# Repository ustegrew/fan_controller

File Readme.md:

# Ventilator control for a laundry

A control system for a fan in a laundry drying room, to exchange humid air for dry air from outside.

## Repository structure

  * [Documentation::Wiki](https://github.com/ustegrew/fan_controller/wiki)
  * [Documentation::Files](https://github.com/ustegrew/fan_controller/tree/master/doc).

## Licenses

Source code is licensed under GPL3, all other content under FDL.

### Source code

    This program is free software: you can redistribute it and/or modify
    it under the terms of the GNU General Public License as published by
    the Free Software Foundation, either version 3 of the License, or
    (at your option) any later version.
	
    This program is distributed in the hope that it will be useful,
    but WITHOUT ANY WARRANTY; without even the implied warranty of
    MERCHANTABILITY or FITNESS FOR A PARTICULAR PURPOSE.  See the
    GNU General Public License for more details.
    
	You should have received a copy of the GNU General Public License
    along with this program.  If not, see <http://www.gnu.org/licenses/>.

### All other content

        Copyright (c)  2017  PETER HOPPE.
    Permission is granted to copy, distribute and/or modify this document
    under the terms of the GNU Free Documentation License, Version 1.3
    or any later version published by the Free Software Foundation;
    with no Invariant Sections, no Front-Cover Texts, and no Back-Cover Texts.
    A copy of the license is included in the section entitled "GNU
    Free Documentation License".

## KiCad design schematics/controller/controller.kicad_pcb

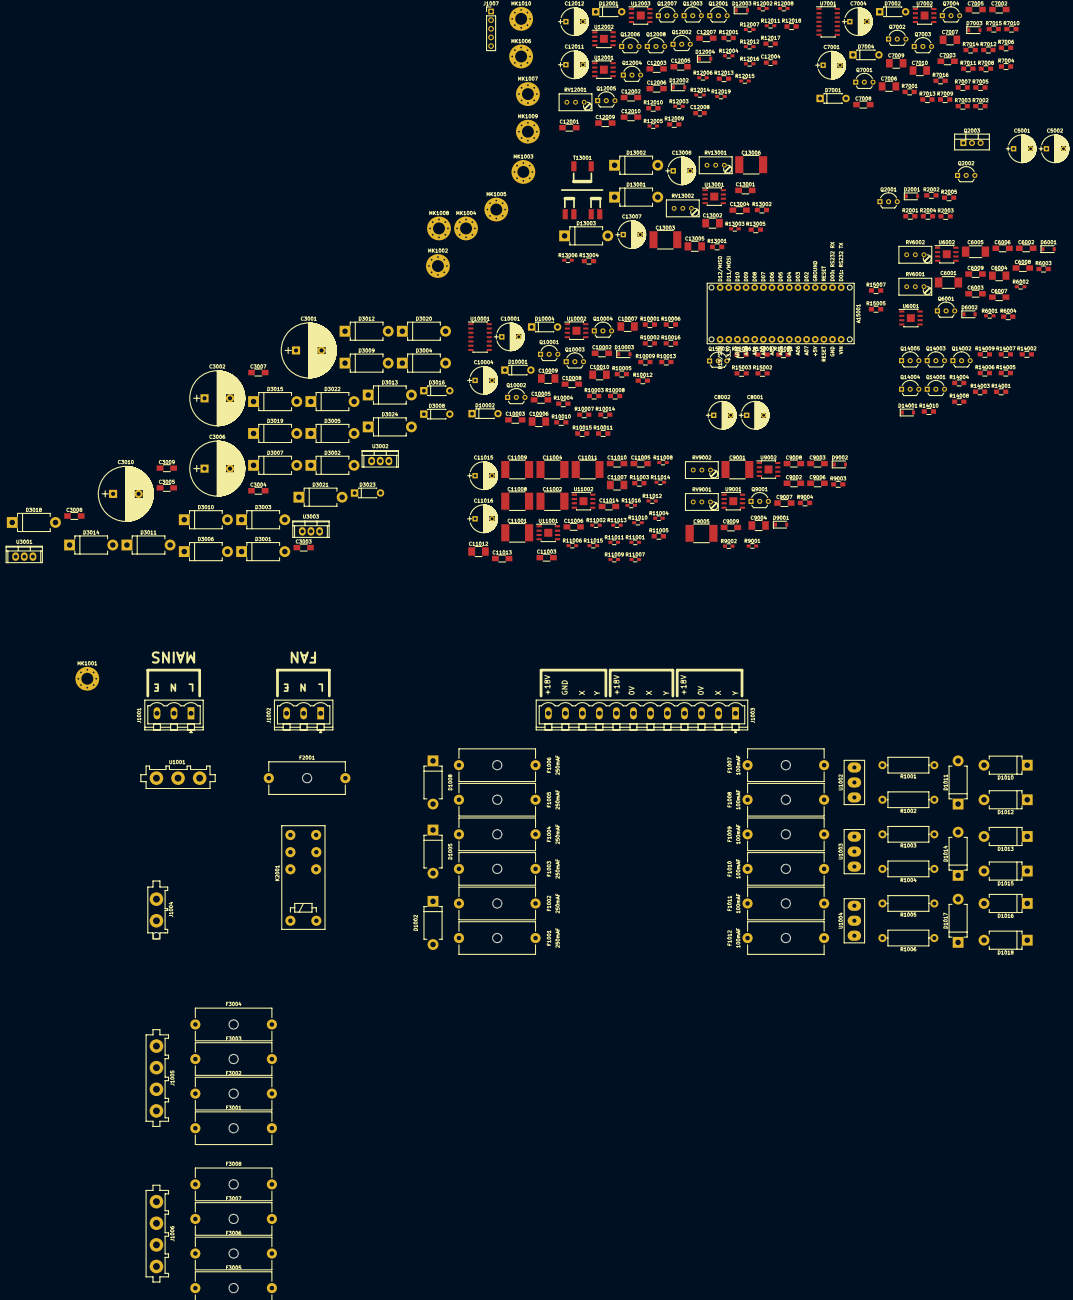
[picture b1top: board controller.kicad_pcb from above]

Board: 2 copper layers, 349 parts (0 on the bottom side), 195 nets, no tracks yet.

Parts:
A15001: Arduino_Nano_v3.x; arduino-nano_3.x
C3001: 1000uF/63V; CP_Radial_D16.0mm_P7.50mm
C3002, C3006, C3010: 470uF/63V; CP_Radial_D16.0mm_P7.50mm
C3003, C3007, C3008, C6002, C6003, C6006, C6007, C7002, C7003, C7005, C7008, C9002, C9003, C9006, C9007, C10002, C10003, C10005, C10008, C11005, C11006, C11013, C11014, C12001, C12002, C12003, C12005, C12006, C12007, C13001, C13004: 100nF; C_1206_HandSoldering
C3004, C3005, C3009, C6008, C9008, C12009, C12010: 1uF; C_1206_HandSoldering
C5001, C5002, C7001, C7004, C8001, C8002, C10001, C10004, C11015, C11016, C12011, C12012, C13007, C13008: 47uF / 63V; CP_Radial_D8.0mm_P5.00mm
C6001, C6005: 2.4nF; C_1812_HandSoldering
C6004, C7006, C7007, C7009, C7010, C9004, C10006, C10007, C10009, C10010, C11007, C11012, C13002, C13005: 4.7uF; C_1210_HandSoldering
C6009, C9009: 0.47uF; C_1206_HandSoldering
C9001, C9005, C11001, C11002, C11004, C11008, C11009, C11011: 1nF; C_2220_HandSoldering
C11003, C11010: 910pF; C_1206_HandSoldering
C12004: 0.22uF; C_0805_HandSoldering
C12008: 39nF; C_0805_HandSoldering
C13003, C13006: 4.7nF; C_2220_HandSoldering
D1002, D1005, D1008: 1.5KE33CA; D_DO-201AD_P12.70mm_Horizontal
D1010, D1011, D1012, D1013, D1014, D1015, D1016, D1017, D1018: 1.5KE30CA; D_DO-201AD_P12.70mm_Horizontal
D2001, D6001, D6002, D7003, D9001, D9002, D10003, D12002, D12003, D12004, D14001: 1N4148; D_SOD-123
D3001, D3004, D3007, D3009, D3012, D3015, D3020, D3024: 1.5KE36CA; D_DO-201AD_P12.70mm_Horizontal
D3002, D3003, D3005, D3006, D3010, D3011, D3013, D3014, D3018, D3019, D3021, D3022: 1N5404; D_DO-201AD_P12.70mm_Horizontal
D3008, D3016, D3023: 1N4007; D_DO-41_SOD81_P7.62mm_Horizontal
D7001, D7002, D7004, D10001, D10002, D10004: BZX85C5V6; D_DO-41_SOD81_P7.62mm_Horizontal
D12001: BZX85C6V2; D_DO-41_SOD81_P7.62mm_Horizontal
D13001, D13002, D13003: 1.5KE12CA; D_DO-201AD_P12.70mm_Horizontal
F1001, F1002, F1003, F1004, F1005, F1006: 250mAF; Fuseholder5x20_horiz_open_Schurter_0031_8201
F1007, F1008, F1009, F1010, F1011, F1012: 100mAF; Fuseholder5x20_horiz_open_Schurter_0031_8201
F2001: 6AT; Fuseholder5x20_horiz_open_Schurter_0031_8201
F3001, F3002: 2AT; Fuseholder5x20_horiz_open_Schurter_0031_8201
F3003, F3004: 1AT; Fuseholder5x20_horiz_open_Schurter_0031_8201
F3005, F3006, F3007, F3008: 1AF; Fuseholder5x20_horiz_open_Schurter_0031_8201
J1001, J1002: Screw_Terminal_01x03; PhoenixContact_MSTBVA-G_03x5.00mm_Vertical
J1003: Periphery; PhoenixContact_MSTBVA-G_12x5.00mm_Vertical
J1004: Conn_01x02_Male; TE_1969799-1
J1005, J1006: Conn_01x04_Male; TE_1969807-1
J1007: FRONTPANEL; Pin_Header_Straight_1x05_Pitch2.54mm
K2001: TE RT424024 (24VDC@1.44kOhm, DPDT, 250VAC, 8A); Relay_DPDT_Schrack-RT2-FormC_RM5.04mm
MK1001, MK1002, MK1003, MK1004, MK1005, MK1006, MK1007, MK1008, MK1009, MK1010: 3.5; MountingHole_3.5mm_Pad_Via
Q2001, Q7004, Q10004, Q12001, Q12002: BC556; TO-92_Inline_Wide
Q2002, Q7001, Q7002, Q7003, Q10001, Q10002, Q10003, Q12003, Q12004, Q12005, Q12006, Q12007, Q12008, Q14001, Q14002, Q14003, Q14004, Q14005, Q15001: BC546C; TO-92_Inline_Wide
Q2003: BD243C; TO-220-3_Vertical
Q6001, Q9001: 2N3819; TO-92_Inline_Wide
R1001, R1002, R1003, R1004, R1005, R1006: 27Ω / 1W; R_Axial_DIN0414_L11.9mm_D4.5mm_P15.24mm_Horizontal
R2001, R2005, R7005, R7006, R7008, R7009, R7016, R10005, R10006, R10008, R10009, R10016, R11003, R12009, R12010, R12013, R12017, R12018, R13004, R13005, R14002, R14003, R14007, R14009, R14010: 100kΩ; R_0805_HandSoldering
R2002, R2003, R7002, R7003, R7004, R7007, R10002, R10003, R10004, R10007, R13001, R13002, R14001, R14004, R14005, R14006, R14008, R15001, R15002, R15003, R15004, R15005, R15006, R15007: 10kΩ; R_0805_HandSoldering
R2004, R6003, R6004, R7001, R7010, R9003, R9004, R10001, R10010, R12001: 4.7kΩ; R_0805_HandSoldering
R6001, R6002: 4.42kΩ; R_0603_HandSoldering
R7011, R7012, R7013, R7014, R7015, R10011, R10012, R10013, R10014, R10015: 1kΩ; R_0805_HandSoldering
R9001, R9002: 6.34kΩ; R_0603_HandSoldering
R11001, R11004: 118kΩ; R_0603_HandSoldering
R11002: 133kΩ; R_0603_HandSoldering
R11005: 49.9kΩ; R_0805_HandSoldering
R11006: 56.2kΩ; R_0603_HandSoldering
R11007: 39.2kΩ; R_0603_HandSoldering
R11008: 46.4kΩ; R_0603_HandSoldering
R11009: 825Ω; R_0603_HandSoldering
R11010: 931Ω; R_0603_HandSoldering
R11011: 1.05kΩ; R_0603_HandSoldering
R11012: 23.7kΩ; R_0603_HandSoldering
R11013: 1.21kΩ; R_0603_HandSoldering
R11014: 27.4kΩ; R_0603_HandSoldering
R11015: 316Ω; R_0603_HandSoldering
R11016: 357Ω; R_0603_HandSoldering
R12002: 68kΩ; R_0603_HandSoldering
R12003, R12004, R12006, R12007, R12008: 22kΩ; R_0603_HandSoldering
R12005: 7.5kΩ; R_0603_HandSoldering
R12011, R12012, R12014, R12015, R12016, R12019: 39kΩ; R_0603_HandSoldering
R13003, R13006: 220Ω; R_0603_HandSoldering
RV6001, RV6002, RV9001, RV9002, RV12001, RV13001, RV13002: 22kΩ; Potentiometer_Trimmer_Bourns_3296W
T13001: Transformer_2P_1S; TRANSFORMER_VENDOR_VACUUMSCHMELZE_T60403-K5032-X102
U1001: Module: surgeprot.mains.275.5.01; TE_1969803-1
U1002, U1003, U1004: Bourns 2026-07-C2LF; Bourns_2026-xx
U3001: L7805; TO-220
U3002: L7815; TO-220
U3003: L7915; TO-220
U6001, U6002, U7002, U9001, U9002, U10002, U12001, U12002, U12003: TL061; SOIC-8-1EP_3.9x4.9mm_Pitch1.27mm
U7001, U10001: 4066; SOIC-14_3.9x8.7mm_Pitch1.27mm
U11001, U11002, U13001: OP282; SOIC-8-1EP_3.9x4.9mm_Pitch1.27mm

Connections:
/comms/DETECTOR_15K_10BAUD_SDA: D14001.2, Q12004.1, Q14003.1, R14005.2
/comms/OSC_15K_UNMUTE_10BAUD_SDA: D7002.1, Q14004.1, R14006.1
/comms/OSC_25K_UNMUTE_10BAUD_SCL: D10002.1, Q14001.3, R14003.1
/comms/VCC: C3005.1, C5001.1, C6002.1, C6003.1, C7005.2, C8001.1, C9002.1, C9003.1, C10005.2, C11005.1, C11006.1, C11015.1, C12001.2, C12003.2, C12005.2, C12011.1, C13001.1, C13007.1, D3016.2, D12001.2, Q7001.1, Q10001.1, R7001.1, R10001.1, R12001.1, R12002.1, R12011.1, R12012.1, R12014.1, R12015.1, U3002.3, U6001.7, U6002.7, U7002.7, U9001.7, U9002.7, U10002.7, U11001.8, U11002.8, U12001.7, U12002.7, U12003.7, U13001.8
/comms/VEE: C3009.2, C5002.2, C6006.1, C6007.1, C7008.2, C8002.2, C9006.1, C9007.1, C10008.2, C11013.1, C11014.1, C11016.2, C12002.2, C12006.2, C12007.2, C12012.2, C13004.1, C13008.2, D3023.1, Q7004.1, Q10004.1, R7010.2, R10010.2, U3003.3, U6001.4, U6002.4, U7002.4, U9001.4, U9002.4, U10002.4, U11001.4, U11002.4, U12001.4, U12002.4, U12003.4, U13001.4
/comms/X: D1010.2, D1011.2, D1013.2, D1014.2, D1016.2, D1017.2, R1001.1, R1003.1, R1005.1, T13001.1
/comms/Y: D1011.1, D1012.2, D1014.1, D1015.2, D1017.1, D1018.2, R1002.1, R1004.1, R1006.1, T13001.2
/comms/comms/barrier/OSC_15K_SIG_OUT_10BAUD_SDA: C7007.1, R13001.2
/comms/comms/barrier/OSC_25K_SIG_OUT_10BAUD_SCL: C10007.1, R13002.2
/comms/comms/detector_15k/IN: C11012.2, C12004.2
/comms/comms/filter_15k/IN: C11007.1, RV13002.3, U13001.7
/comms/comms/osc_15k/osc_15k/osc/OUT: C6004.1, R7011.2
/comms/comms/osc_25k/osc_25k/osc/OUT: C9004.1, R10011.2
/comms_router/CPU_10BAUD_SCL: A15001.6, R14001.2, R15005.2
/comms_router/CPU_10BAUD_SDA: A15001.5, R14004.2, R15006.2
/comms_router/CPU_10BAUD_WR_EN: A15001.7, R14008.2, R15004.2
/comms_router/V_LOGIC: A15001.27, C3004.1, D3008.2, J1007.4, Q14001.1, Q14002.1, R14005.1, R14007.1, R15001.1, R15002.1, R15003.1, R15004.1, R15005.1, R15006.1, U3001.3
/cpu/CPU_HIBAUD_SCL: A15001.24, J1007.1, R15001.2
/cpu/CPU_HIBAUD_SDA: A15001.23, J1007.2, R15002.2
/cpu/FAN_ON: A15001.8, R2003.1, R15003.2
/cpu/RESET: J1007.3, R15007.1
/fan-switch/L: F2001.1, J1001.1, U1001.1
/fan-switch/LFAN: J1002.1, K2001.24
/fan-switch/N: J1001.2, J1004.1, K2001.11, U1001.2
/fan-switch/NFAN: J1002.2, K2001.14
/psu/TR01-1: F3001.1, J1005.1
/psu/TR01-2: F3002.1, J1005.2
/psu/TR01-3: F3003.1, J1005.3
/psu/TR01-4: F3004.1, J1005.4
/psu/TR02-1: F3005.1, J1006.1
/psu/TR02-2: F3006.1, J1006.2
/psu/TR02-3: F3007.1, J1006.3
/psu/TR02-4: F3008.1, J1006.4
/psu/V_DCDC_+18: C3001.1, D1002.2, D1005.2, D1008.2, D2001.1, D3003.1, D3006.1, F1001.1, F1003.1, F1005.1, K2001.A2, Q2001.3, R2001.1
Earth: A15001.4, A15001.29, C3001.2, C3002.2, C3003.2, C3004.2, C3005.2, C3006.2, C3007.2, C3008.1, C3009.1, C3010.1, C5001.2, C5002.1, C6002.2, C6003.2, C6006.2, C6007.2, C7001.2, C7002.2, C7003.1, C7004.1, C7005.1, C7008.1, C7009.2, C7010.2, C8001.2, C8002.1, C9002.2, C9003.2, C9006.2, C9007.2, C10001.2, C10002.2, C10003.1, C10004.1, C10005.1, C10008.1, C10009.2, C10010.2, C11005.2, C11006.2, C11013.2, C11014.2, C11015.2, C11016.1, C12001.1, C12002.1, C12003.1, C12005.1, C12006.1, C12007.1, C12008.2, C12009.2, C12010.2, C12011.2, C12012.1, C13001.2, C13003.1, C13004.2, C13006.1, C13007.2, C13008.1, D1002.1, D1005.1, D1008.1, D1010.1, D1012.1, D1013.1, D1015.1, D1016.1, D1018.1, D3001.1, D3002.2, D3005.2, D3007.2, D3009.1, D3010.2, D3013.2, D3015.2, D3020.1, D3024.2, D7001.2, D7004.1, D10001.2, D10004.1, D13001.2, D13003.1, F1002.1, F1004.1, F1006.1, F3006.2, F3007.2, J1001.3, J1002.3, J1007.5, MK1001.1, MK1002.1, MK1003.1, MK1004.1, MK1005.1, MK1006.1, MK1007.1, MK1008.1, MK1009.1, MK1010.1, Q2002.3, Q2003.3, Q12002.1, Q12003.3, Q12004.3, Q12007.3, Q12008.3, Q14003.3, Q14004.3, Q14005.3, Q15001.3, R2005.2, R7016.2, R10016.2, R11009.2, R11010.2, R11011.2, R11013.2, R11015.2, R11016.2, R12004.2, R12008.2, R12009.2, R12010.2, R12016.2, R12019.2, R13004.1, R13005.2, R14002.2, R14003.2, R14009.2, R14010.2, RV12001.3, RV13001.3, RV13002.1, T13001.4, T13001.5, U1002.2, U1003.2, U1004.2, U3001.2, U3002.2, U3003.1, U11001.3, U11001.5
unnamed: A15001.3, A15001.28, Q15001.1
unnamed: C3002.1, C3003.1, D3008.1, D3011.1, D3014.1, U3001.1
unnamed: C3006.1, C3007.1, D3016.1, D3019.1, D3022.1, U3002.1
unnamed: C3008.2, C3010.2, D3018.2, D3021.2, D3023.2, U3003.2
unnamed: C6001.1, R6003.1, RV6001.1, U6001.6, U6002.3
unnamed: C6001.2, R6001.1
unnamed: C6004.2, U6002.2, U6002.6
unnamed: C6005.1, R6001.2, R6002.1, U6001.3
unnamed: C6005.2, C6009.2, D6002.1, Q6001.3, R6002.2, R6004.2, RV6002.3
unnamed: C6008.1, R6003.2
unnamed: C6008.2, D6001.1, D6002.2
unnamed: C6009.1, D6001.2, R6004.1, RV6002.1
unnamed: C7001.1, D7001.1, R7001.2, R7002.2
unnamed: C7002.1, Q7001.3, R7003.1, R7004.1, U7001.14
unnamed: C7003.2, D7003.2, Q7002.3, Q7003.3, Q7004.3, U7001.7
unnamed: C7004.2, D7004.2, R7007.2, R7010.1
unnamed: C7006.1, R7016.1, U7002.3
unnamed: C7006.2, R7015.1
unnamed: C7007.2, U7002.2, U7002.6
unnamed: C7009.1, U7001.9
unnamed: C7010.1, U7001.10
unnamed: C9001.1, R9003.1, RV9001.1, U9001.6, U9002.3
unnamed: C9001.2, R9001.1
unnamed: C9004.2, U9002.2, U9002.6
unnamed: C9005.1, R9001.2, R9002.1, U9001.3
unnamed: C9005.2, C9009.2, D9002.1, Q9001.3, R9002.2, R9004.2, RV9002.3
unnamed: C9008.1, R9003.2
unnamed: C9008.2, D9001.1, D9002.2
unnamed: C9009.1, D9001.2, R9004.1, RV9002.1
unnamed: C10001.1, D10001.1, R10001.2, R10002.2
unnamed: C10002.1, Q10001.3, R10003.1, R10004.1, U10001.14
unnamed: C10003.2, D10003.2, Q10002.3, Q10003.3, Q10004.3, U10001.7
unnamed: C10004.2, D10004.2, R10007.2, R10010.1
unnamed: C10006.1, R10016.1, U10002.3
unnamed: C10006.2, R10015.1
unnamed: C10007.2, U10002.2, U10002.6
unnamed: C10009.1, U10001.9
unnamed: C10010.1, U10001.10
unnamed: C11001.1, C11008.1, R11005.2, R11009.1
unnamed: C11001.2, R11001.1, R11006.1, U11001.1
unnamed: C11002.1, C11009.1, R11006.2, R11010.1
unnamed: C11002.2, R11002.1, R11007.1, U11001.7
unnamed: C11003.1, C11010.1, R11007.2, R11011.1
unnamed: C11003.2, R11003.1, R11008.1, R11012.1, U11002.1
unnamed: C11004.1, C11011.1, R11008.2, R11013.1
unnamed: C11004.2, C11012.1, R11004.1, R11014.1, U11002.7
unnamed: C11007.2, R11005.1
unnamed: C11008.2, R11001.2, U11001.2
unnamed: C11009.2, R11002.2, U11001.6
unnamed: C11010.2, R11003.2, U11002.2
unnamed: C11011.2, R11004.2, U11002.6
unnamed: C12004.1, R12009.1, U12002.3
unnamed: C12008.1, Q12001.1, Q12003.1, U12001.3, U12003.2
unnamed: C12009.1, Q12005.2, R12014.2, R12016.1
unnamed: C12010.1, Q12006.2, R12015.2, R12019.1
unnamed: C13002.1, C13003.2, R13003.2
unnamed: C13002.2, RV13001.1, U13001.1
unnamed: C13005.1, C13006.2, R13006.1
unnamed: C13005.2, R13005.1, U13001.5
unnamed: D2001.2, K2001.A1, Q2003.2
unnamed: D3001.2, D3002.1, D3003.2, D3004.2, F3001.2
unnamed: D3004.1, D3005.1, D3006.2, D3007.1, F3002.2
unnamed: D3009.2, D3010.1, D3011.2, D3012.2, F3003.2
unnamed: D3012.1, D3013.1, D3014.2, D3015.1, F3004.2
unnamed: D3018.1, D3019.2, D3020.2, F3005.2
unnamed: D3021.1, D3022.2, D3024.1, F3008.2
unnamed: D7002.2, R7005.2
unnamed: D7003.1, Q7002.2, R7005.1
unnamed: D10002.2, R10005.2
unnamed: D10003.1, Q10002.2, R10005.1
unnamed: D12001.1, Q12002.2, R12004.1
unnamed: D12002.1, Q12008.2, R12018.2
unnamed: D12002.2, R12003.2
unnamed: D12003.1, Q12007.2, R12017.1
unnamed: D12003.2, R12007.2
unnamed: D12004.1, Q12003.2, R12010.1
unnamed: D12004.2, R12006.2
unnamed: D13001.1, D13002.1, R13003.1, T13001.3
unnamed: D13002.2, D13003.2, R13006.2, T13001.6
unnamed: D14001.1, Q14002.2, R14004.1
unnamed: F1001.2, J1003.1
unnamed: F1002.2, J1003.2
unnamed: F1003.2, J1003.5
unnamed: F1004.2, J1003.6
unnamed: F1005.2, J1003.9
unnamed: F1006.2, J1003.10
unnamed: F1007.1, R1001.2, U1002.1
unnamed: F1007.2, J1003.3
unnamed: F1008.1, R1002.2, U1002.3
unnamed: F1008.2, J1003.4
unnamed: F1009.1, R1003.2, U1003.1
unnamed: F1009.2, J1003.7
unnamed: F1010.1, R1004.2, U1003.3
unnamed: F1010.2, J1003.8
unnamed: F1011.1, R1005.2, U1004.1
unnamed: F1011.2, J1003.11
unnamed: F1012.1, R1006.2, U1004.3
unnamed: F1012.2, J1003.12
unnamed: F2001.2, K2001.21
unnamed: J1004.2, U1001.3
unnamed: Q2001.1, R2004.1, R2005.1
unnamed: Q2001.2, R2002.2
unnamed: Q2002.1, R2001.2, R2002.1
unnamed: Q2002.2, R2003.2
unnamed: Q2003.1, R2004.2
unnamed: Q6001.1, RV6001.3
unnamed: Q6001.2, RV6002.2
unnamed: Q7001.2, R7002.1
unnamed: Q7002.1, R7003.2, R7006.2, R7008.1
unnamed: Q7003.1, R7004.2, R7009.1
unnamed: Q7003.2, R7006.1
unnamed: Q7004.2, R7007.1
unnamed: Q9001.1, RV9001.3
unnamed: Q9001.2, RV9002.2
unnamed: Q10001.2, R10002.1
unnamed: Q10002.1, R10003.2, R10006.2, R10008.1
unnamed: Q10003.1, R10004.2, R10009.1
unnamed: Q10003.2, R10006.1
unnamed: Q10004.2, R10007.1
unnamed: Q12001.2, Q12002.3
unnamed: Q12001.3, R12001.2
unnamed: Q12004.2, R12013.2
unnamed: Q12005.1, R12011.2, R12018.1
unnamed: Q12005.3, Q12007.1
unnamed: Q12006.1, R12012.2, R12013.1, R12017.2
unnamed: Q12006.3, Q12008.1
unnamed: Q14001.2, R14001.1, R14002.1
unnamed: Q14002.3, R14006.2, R14010.1
unnamed: Q14003.2, Q14005.2, R14008.1, R14009.1
unnamed: Q14004.2, Q14005.1, R14007.2
unnamed: Q15001.2, R15007.2
unnamed: R7008.2, U7001.5, U7001.13
unnamed: R7009.2, U7001.6, U7001.12
unnamed: R7011.1, U7001.1
unnamed: R7012.1, R7013.2, U7001.8
unnamed: R7012.2, U7001.2
unnamed: R7013.1, U7001.4
unnamed: R7014.1, R7015.2, U7001.11
unnamed: R7014.2, U7001.3
unnamed: R10008.2, U10001.5, U10001.13
unnamed: R10009.2, U10001.6, U10001.12
unnamed: R10011.1, U10001.1
unnamed: R10012.1, R10013.2, U10001.8
unnamed: R10012.2, U10001.2
unnamed: R10013.1, U10001.4
unnamed: R10014.1, R10015.2, U10001.11
unnamed: R10014.2, U10001.3
unnamed: R11012.2, R11015.1, U11002.3
unnamed: R11014.2, R11016.1, U11002.5
unnamed: R12002.2, R12005.1, U12001.2
unnamed: R12003.1, U12001.6
unnamed: R12005.2, R12008.1, U12003.3
unnamed: R12006.1, RV12001.1, U12002.6
unnamed: R12007.1, U12003.6
unnamed: R13001.1, R13002.1, R13004.2, U13001.3
unnamed: RV6001.2, U6001.2
unnamed: RV9001.2, U9001.2
unnamed: RV12001.2, U12002.2
unnamed: RV13001.2, U13001.2
unnamed: RV13002.2, U13001.6

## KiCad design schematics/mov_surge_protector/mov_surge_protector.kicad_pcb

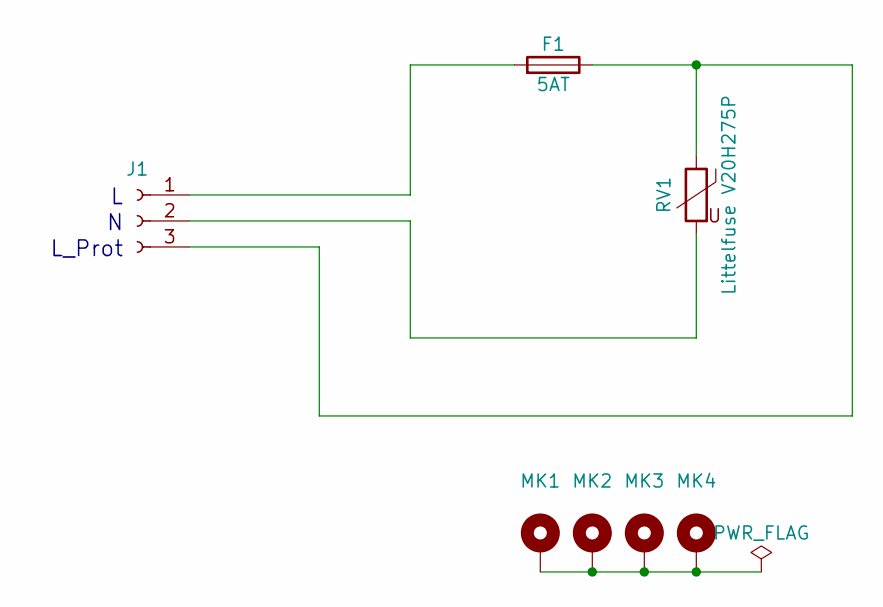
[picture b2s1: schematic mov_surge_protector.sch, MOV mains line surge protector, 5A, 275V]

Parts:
F1: 5AT; Fuseholder5x20_horiz_open_lateral_Type-II
J1: Conn_01x03_Female; MOV_Surge_Protector
MK1, MK2, MK3, MK4: Mounting_Hole_PAD; SolderWirePad_single_1-5mmDrill
RV1: Littelfuse V20H275P; RV_Disc_D21.5_W5.6_P10

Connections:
unnamed: F1.1, J1.3, RV1.1
unnamed: F1.2, J1.1
unnamed: J1.2, RV1.2
unnamed: MK1.1, MK2.1, MK3.1, MK4.1

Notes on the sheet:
L_Prot

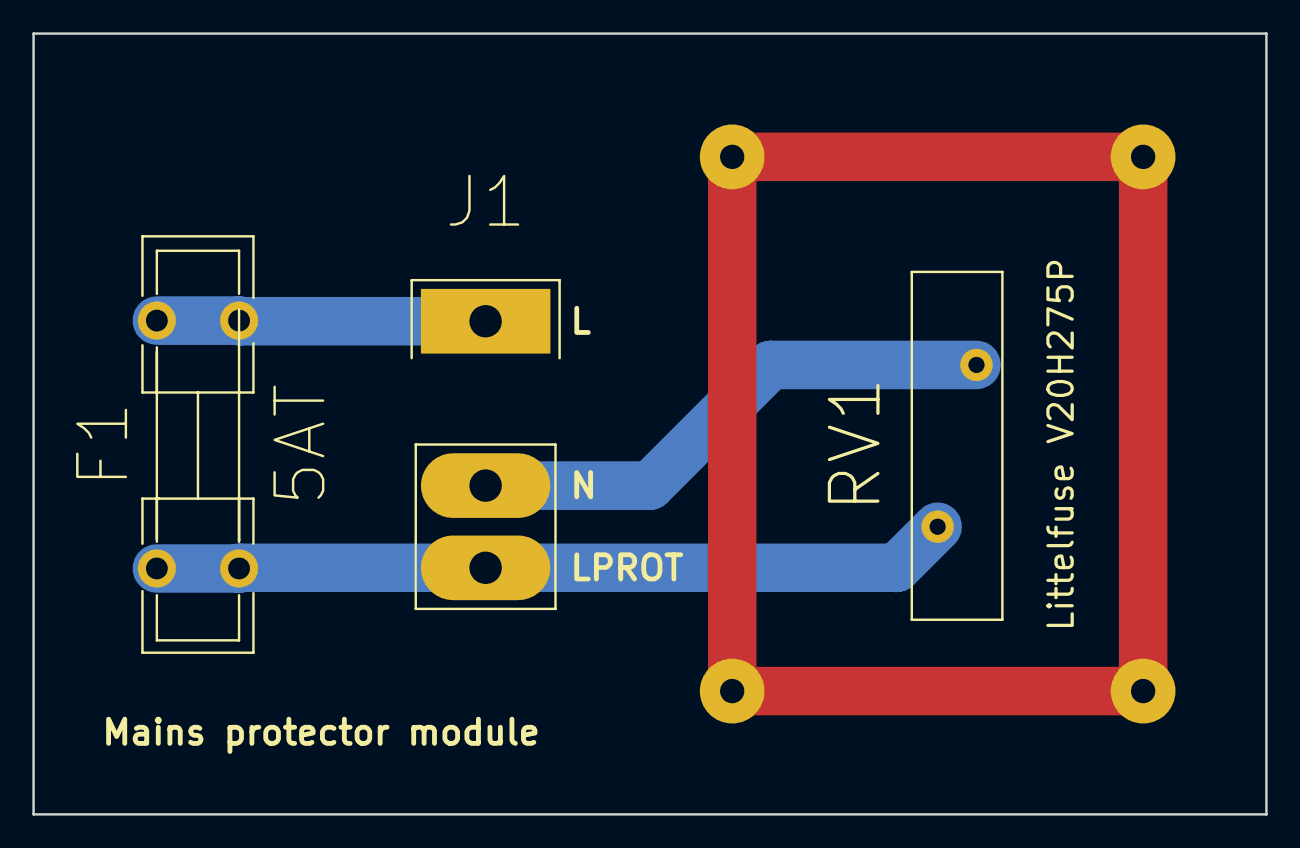
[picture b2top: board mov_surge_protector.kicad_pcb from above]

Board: 2 copper layers, 76.2 x 48.3 mm, 7 parts (0 on the bottom side), 4 nets.

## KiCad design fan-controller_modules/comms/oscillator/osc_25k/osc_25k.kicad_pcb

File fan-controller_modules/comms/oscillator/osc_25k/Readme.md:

# Eval: Oscillator, 25kHz

KiCad project for an evaluation board providing a 25kHz mutable oscillator. Oscillator is based on an AGC stabilized Wien Bridge. Muting via a CD4066 analog switch.

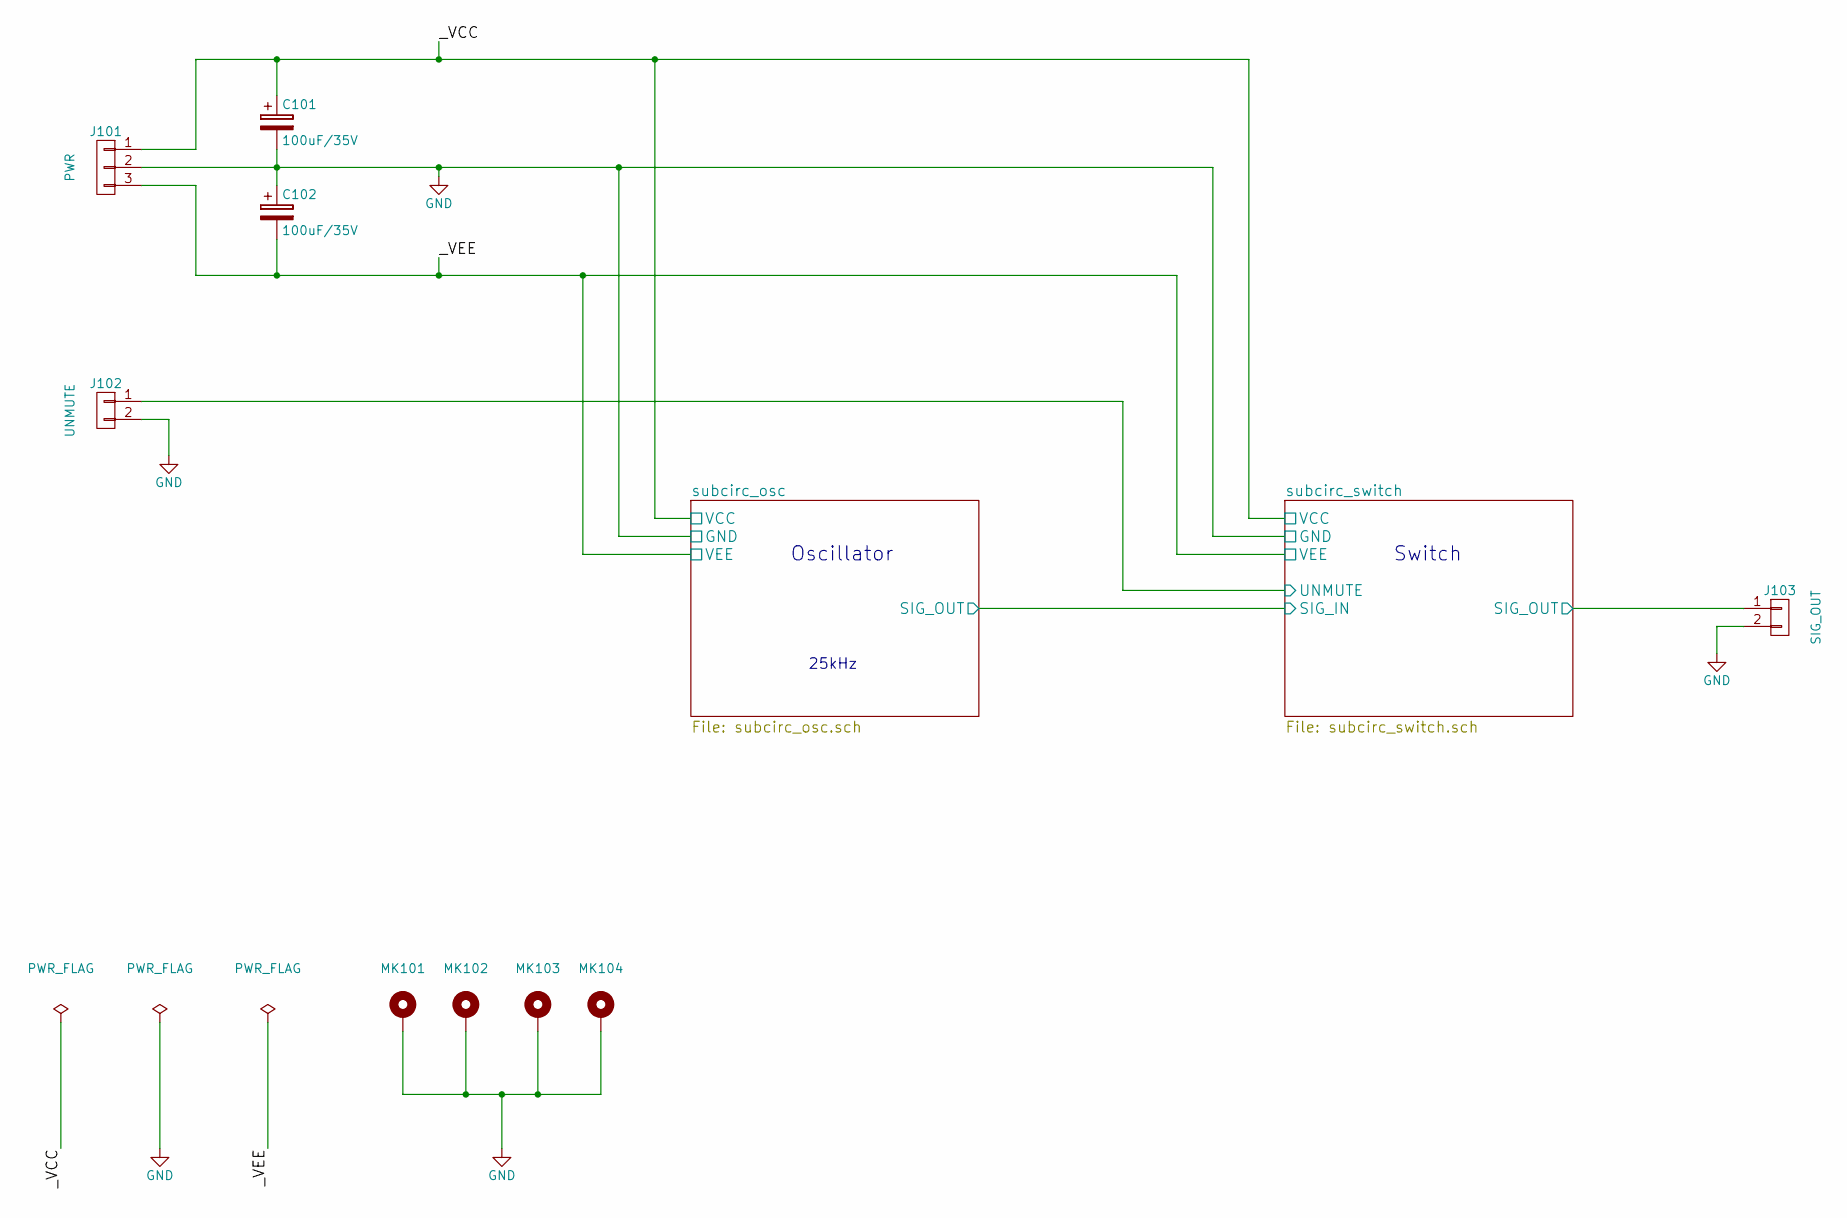
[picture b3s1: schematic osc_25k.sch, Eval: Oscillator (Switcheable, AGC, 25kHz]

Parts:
C101, C102: 100uF/35V; CP_Elec_6.3x7.7
J101: PWR; Pin_Header_Straight_1x03_Pitch2.54mm
J102: UNMUTE; Pin_Header_Straight_1x02_Pitch2.54mm
J103: SIG_OUT; Pin_Header_Straight_1x02_Pitch2.54mm
MK101, MK102, MK103, MK104: MountingHole_3.5mm_Pad_Via

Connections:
/_VCC: C101.1, J101.1; also elsewhere on the board
/_VEE: C102.2, J101.3; also elsewhere on the board
/subcirc_switch/SIG_OUT: J103.1; also elsewhere on the board
/subcirc_switch/UNMUTE: J102.1; also elsewhere on the board
GND: C101.2, C102.1, J101.2, J102.2, J103.2, MK101.1, MK102.1, MK103.1, MK104.1; also elsewhere on the board

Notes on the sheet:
Oscillator
Switch
25kHz

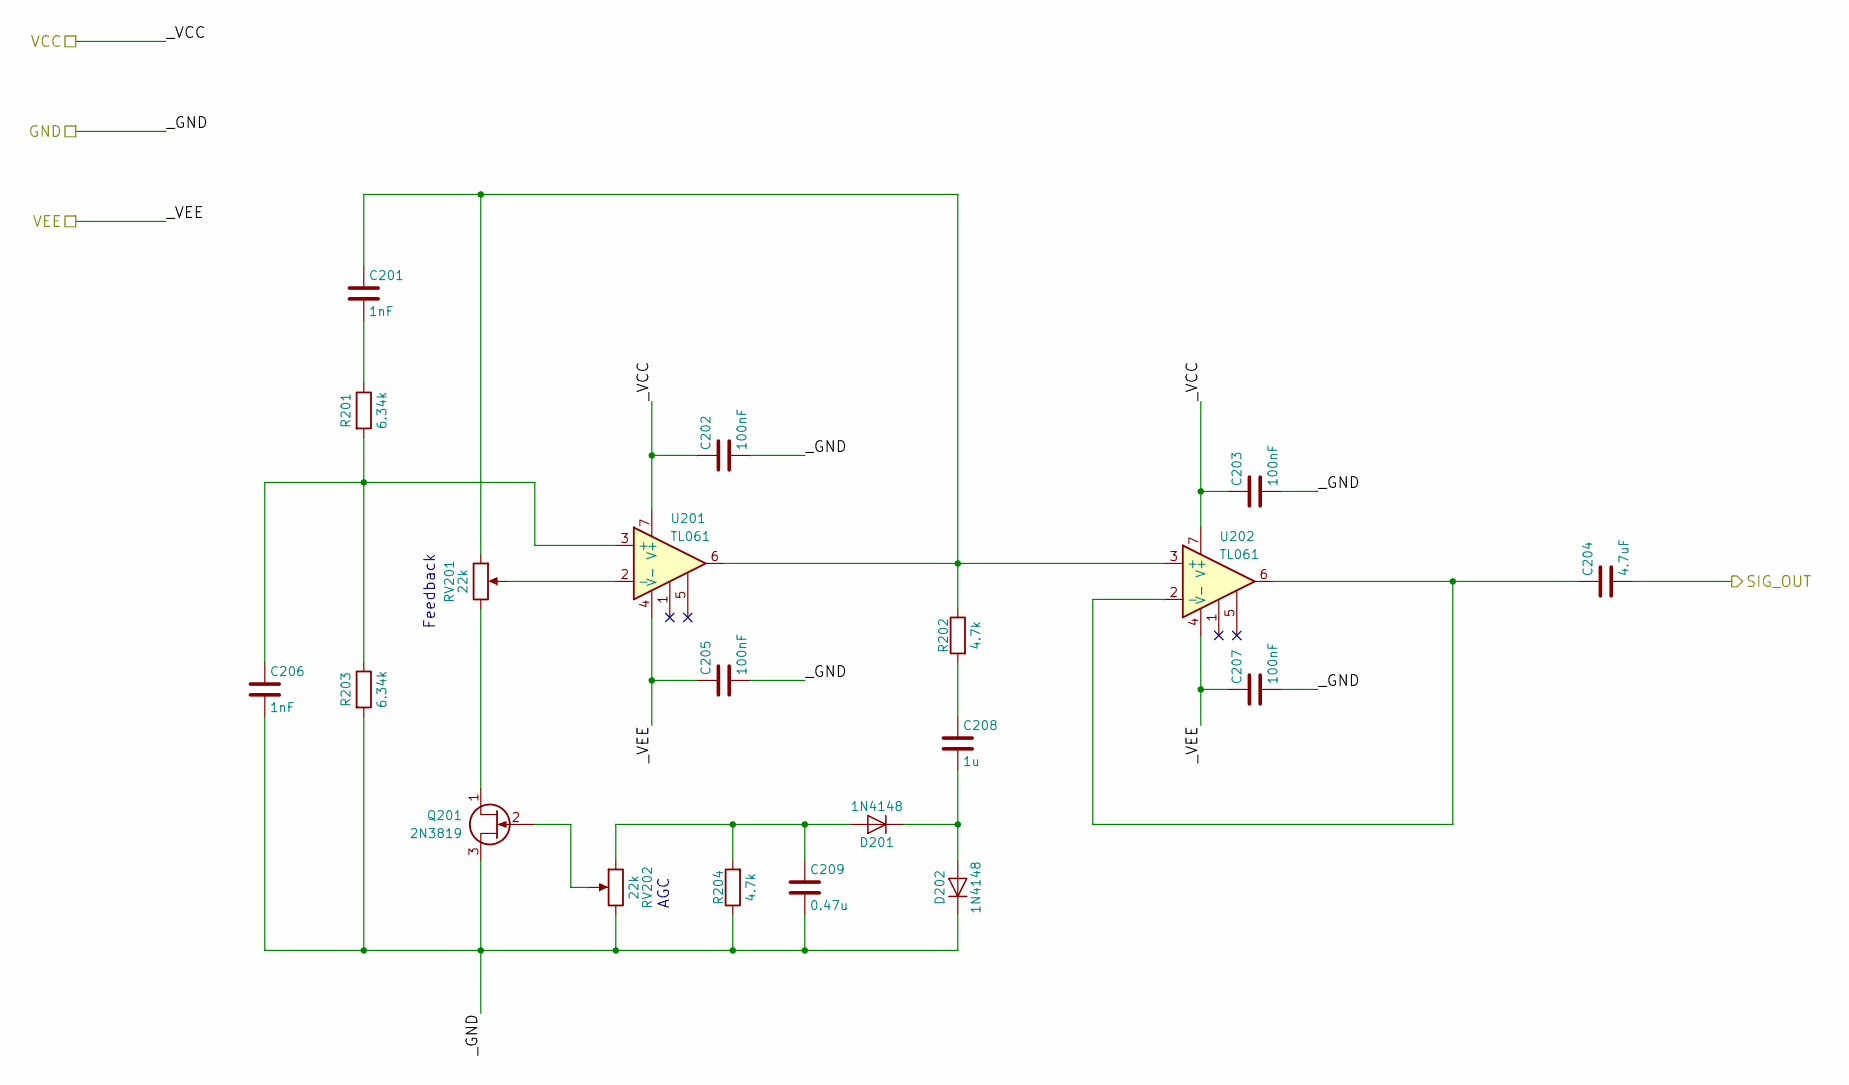
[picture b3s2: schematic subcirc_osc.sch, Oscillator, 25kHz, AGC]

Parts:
C201, C206: 1nF; C_1206_HandSoldering
C202, C203, C205, C207: 100nF; C_1812_HandSoldering
C204: 4.7uF; C_1206_HandSoldering
C208: 1u; C_1210_HandSoldering
C209: 0.47u; C_1812_HandSoldering
D201, D202: 1N4148; D_DO-35_SOD27_P7.62mm_Horizontal
Q201: 2N3819; TO-92_Inline_Narrow_Oval
R201, R203: 6.34k; R_0201
R202, R204: 4.7k; R_0201
RV201, RV202: 22k; Potentiometer_Trimmer_Bourns_3296W
U201, U202: TL061; SOIC-8_3.9x4.9mm_Pitch1.27mm

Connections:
/_VCC: C202.1, C203.1, U201.7 (V+), U202.7 (V+); also elsewhere on the board
/_VEE: C205.1, C207.1, U201.4 (V-), U202.4 (V-); also elsewhere on the board
/subcirc_switch/SIG_IN: C204.2; also elsewhere on the board
GND: C202.2, C203.2, C205.2, C206.2, C207.2, C209.2, D202.1 (K), Q201.3 (S), R203.2, R204.1, RV202.3; also elsewhere on the board
unnamed: C201.1, R202.1, RV201.1, U201.6, U202.3 (+)
unnamed: C201.2, R201.1
unnamed: C204.1, U202.2 (-), U202.6
unnamed: C206.1, R201.2, R203.1, U201.3 (+)
unnamed: C208.1, R202.2
unnamed: C208.2, D201.1 (K), D202.2 (A)
unnamed: C209.1, D201.2 (A), R204.2, RV202.1
unnamed: Q201.1 (D), RV201.3
unnamed: Q201.2 (G), RV202.2
unnamed: RV201.2, U201.2 (-)

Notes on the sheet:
Feedback
AGC

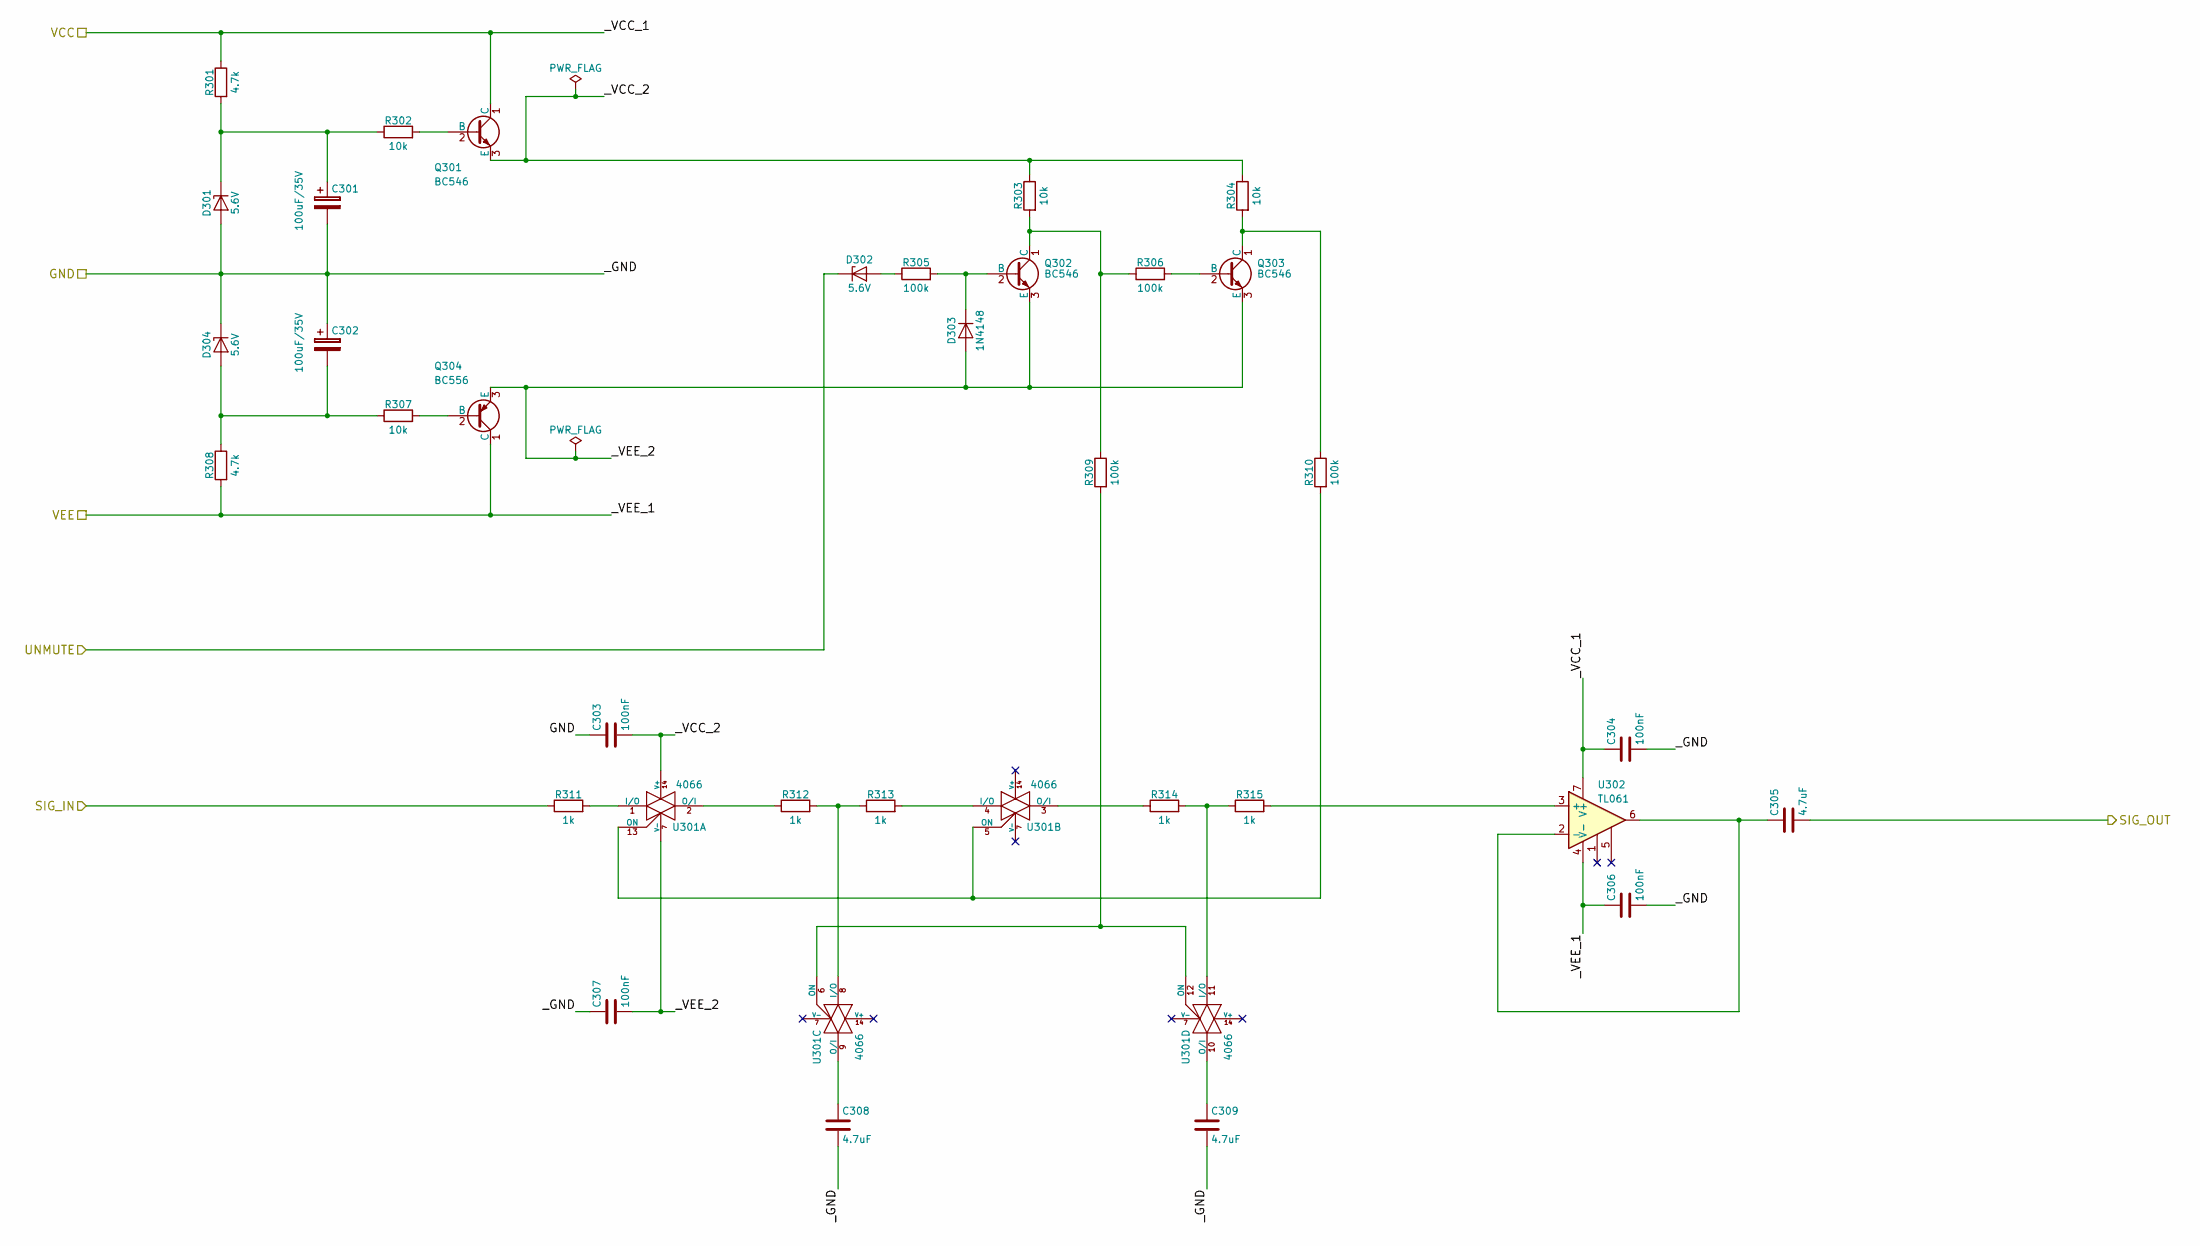
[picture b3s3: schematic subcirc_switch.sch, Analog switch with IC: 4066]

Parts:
C301, C302: 100uF/35V; CP_Elec_6.3x7.7
C303, C304, C306, C307: 100nF; C_1812_HandSoldering
C305, C308, C309: 4.7uF; C_1206_HandSoldering
D301, D302, D304: 5.6V; D_SOD-523
D303: 1N4148; D_DO-35_SOD27_P7.62mm_Horizontal
Q301, Q302, Q303: BC546; TO-92_Inline_Narrow_Oval
Q304: BC556; TO-92_Inline_Narrow_Oval
R301, R308: 4.7k; R_0201
R302, R303, R304, R307: 10k; R_0603_HandSoldering
R305, R306, R309, R310: 100k; R_0201
R311, R312, R313, R314, R315: 1k; R_0201
U301: 4066; SOIC-14_3.9x8.7mm_Pitch1.27mm
U302: TL061; SOIC-8_3.9x4.9mm_Pitch1.27mm

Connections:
/_VCC: C304.1, Q301.1 (C), R301.1, U302.7 (V+); also elsewhere on the board
/_VEE: C306.1, Q304.1 (C), R308.2, U302.4 (V-); also elsewhere on the board
/subcirc_switch/SIG_IN: R311.1; also elsewhere on the board
/subcirc_switch/SIG_OUT: C305.2; also elsewhere on the board
/subcirc_switch/UNMUTE: D302.1 (K); also elsewhere on the board
/subcirc_switch/_VCC_2: C303.2, Q301.3 (E), R303.1, R304.1, U301.14 (V+)
/subcirc_switch/_VEE_2: C307.2, D303.2 (A), Q302.3 (E), Q303.3 (E), Q304.3 (E), U301.7 (V-)
GND: C301.2, C302.1, C303.1, C304.2, C306.2, C307.1, C308.2, C309.2, D301.2 (A), D304.1 (K); also elsewhere on the board
unnamed: C301.1, D301.1 (K), R301.2, R302.1
unnamed: C302.2, D304.2 (A), R307.1, R308.1
unnamed: C305.1, U302.2 (-), U302.6
unnamed: C308.1, U301.9 (O/I)
unnamed: C309.1, U301.10 (O/I)
unnamed: D302.2 (A), R305.1
unnamed: D303.1 (K), Q302.2 (B), R305.2
unnamed: Q301.2 (B), R302.2
unnamed: Q302.1 (C), R303.2, R306.1, R309.1
unnamed: Q303.1 (C), R304.2, R310.1
unnamed: Q303.2 (B), R306.2
unnamed: Q304.2 (B), R307.2
unnamed: R309.2, U301.6 (ON), U301.12 (ON)
unnamed: R310.2, U301.5 (ON), U301.13 (ON)
unnamed: R311.2, U301.1 (I/O)
unnamed: R312.1, U301.2 (O/I)
unnamed: R312.2, R313.1, U301.8 (I/O)
unnamed: R313.2, U301.4 (I/O)
unnamed: R314.1, U301.3 (O/I)
unnamed: R314.2, R315.1, U301.11 (I/O)
unnamed: R315.2, U302.3 (+)

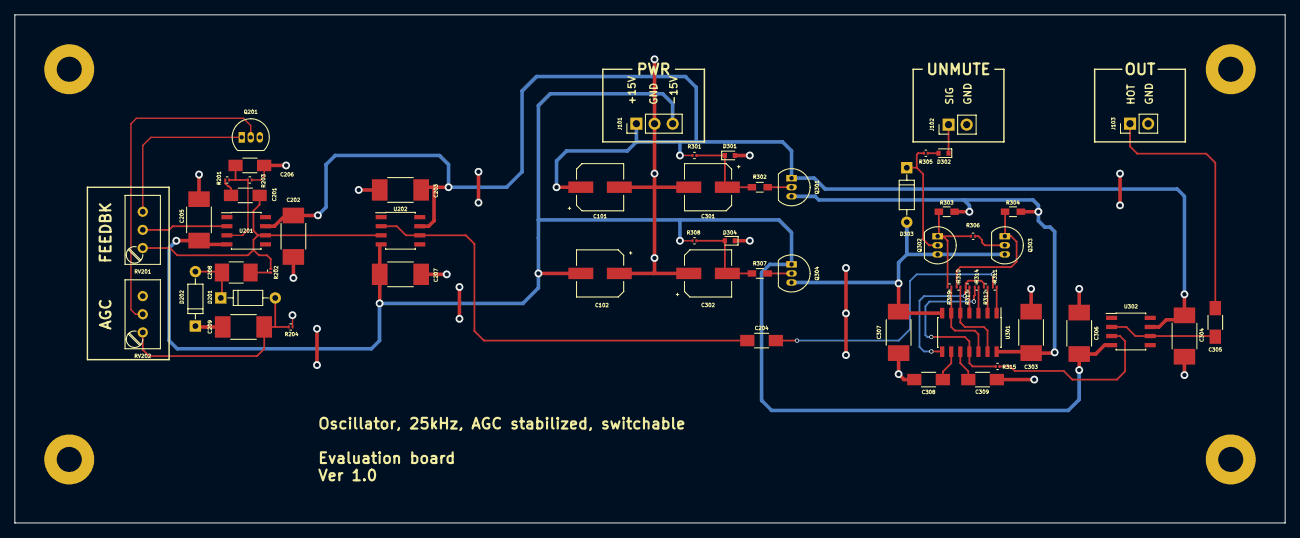
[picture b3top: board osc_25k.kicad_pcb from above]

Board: 2 copper layers, 177.8 x 71.1 mm, 63 parts (0 on the bottom side), 39 nets.
